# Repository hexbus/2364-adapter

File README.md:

# 2364 / 68764 ROM adapter

A compact **23 × 37 mm** adapter for replacing a 24-pin, active-low-select
2364 or MCM68764 ROM with a **28-pin AT28C64B EEPROM or 5 V 2764/27C64 EPROM**.
Designed by **Jon Guidry / hexbus** for the TI-99/4A Hexbus interface.

All 13 address lines and 8 data lines pass through without rearranging the
ROM image. Host pin 20 drives both `/CE` and `/OE`; replacement pin 27 is
held high to disable writing/programming. Program the memory separately.

## Top and bottom

| Top — components and ROM socket | Bottom — pins toward the host |
| --- | --- |
|  |  |

Previews show the delivered Gerbers; the bottom is viewed from underneath.
**C1, JP1 and `U1 NOTCH` identify the top. `J1 TO HOST` identifies the bottom.**
Each connector has its own square pin-1 pad; their positions are offset.
Both notch ends face the same end of the board.
The notched top silkscreen outline encloses all 28 memory pads and is centered
on the two U1 pin rows; the notch is at the pin-1 end.

[Photo of the first bare boards](images/first-boards.jpg): top on the left,
bottom on the right. Those boards predate the printed designer credit and top outline.
For my own batches, I also use JLCPCB's order-time QR option for identifiers
such as `JDG001`–`JDG025`. Public Gerbers include permanent
`hexbus.com (c) 2026` credit so boards made by others are identified too.

## Files and fabrication

- **[Download the Gerber ZIP — Rev A with full top outline, 9 November 2026](https://github.com/hexbus/2364-adapter/raw/refs/heads/main/gerbers/2364-adapter-rev-a-full-outline-20261109.zip)**
- **[Order at JLCPCB using my referral link](https://jlcpcb.com/?from=RVDYTTLKZHK)**
- [KiCad 10 project](hardware/68764-to-28pin.kicad_pro),
  [schematic](hardware/68764-to-28pin.kicad_sch) and [BOM](hardware/bom.csv)

Download the Gerber ZIP, open JLCPCB through the referral link, and upload
the ZIP. Select **2 layers, 1.6 mm FR4 and 1 oz copper**; confirm the detected
board size is **23 × 37 mm** before ordering. The referral link does not
upload the files automatically. I may receive referral rewards for qualifying
new users.

Order **2 layers, 1.6 mm FR4, 1 oz copper, 23 × 37 mm**, with solder mask
on both sides and HASL or ENIG finish. Component holes are specified as
**0.80 mm plated through holes**. Minimum track width is 0.25 mm; design
clearance is 0.20 mm. No stencil or assembly files are included.

This package retains the October 21 mask correction, adds bottom designer
credit, includes a notched outline for the top memory, and moves C1/JP1 labels
clear of the mask openings. Copper, masks,
drill geometry and outline match corrected Rev A. **Do not fabricate the
original October 19 package:** its connector pads lacked mask openings.

## JP1 and C1

| Installed memory | JP1 | Effect |
| --- | --- | --- |
| AT28C64B, DIP28 | **OPEN** | Pin 1 isolated; pin 27 `/WE` held high |
| 5 V 2764 / 27C64, DIP28 | **CLOSED** with solder | Pin 1 VPP at +5 V for reading; pin 27 `/PGM` high |

**C1: 100 nF (0.1 µF), 0805 ceramic, X7R or X5R, at least 16 V.**
It bypasses +5 V to ground and is nonpolarized: either orientation is correct.
Change JP1 only with power removed. Other EEPROM models need their exact
datasheet checked; this does not cover every part called “2864.”

## Assembly

1. Solder C1 and set JP1 first; the memory body will cover them.
2. Fit **two 1×12 round-pin male strips underneath**, pins pointing toward
   the host; solder from above. Use socket-compatible mating pins around
   0.45–0.50 mm diameter, not thick square headers.
3. Fit **two 1×14 female socket strips on top**, 2.54 mm pitch and 15.24 mm
   between rows; solder underneath. A closed-base DIP socket can foul the
   other connector's solder tails, so use separate strips.
4. Keep top tails at least 0.5 mm below the memory body and underside tails
   at least 0.5 mm clear of exposed metal in the host. Check actual strip
   dimensions, pin engagement and enclosure clearance before seating.
5. With no memory installed, check the pin map below. J1 pins 24 and 12 must
   have no sustained short; C1 may cause a brief meter response.
6. Program and verify the memory separately, then insert it with U1 pin 1
   at its square pad. With host power off, align J1 pin 1 with the original
   socket's pin 1. Check clearance and do not force it.

Never apply programming voltage through the 24-pin host connector.

## Pinout and continuity checks

Package pin numbers are **viewed from the top**. The bottom footprint is
already flipped correctly in CAD; do not reverse its numbering again.
Grouped entries correspond in the order shown.

| J1: 2364 / 68764 host | Signal | U1: 28-pin memory |
| --- | --- | --- |
| 1–8 | A7, A6, A5, A4, A3, A2, A1, A0 | 3–10 |
| 9–11 | D0, D1, D2 | 11–13 |
| 12 | Ground | 14; C1 ground pad |
| 13–17 | D3, D4, D5, D6, D7 | 15–19 |
| 18 | A11 | 23 |
| 19 | A10 | 21 |
| 20 | Active-low select | 20 (`/CE`) and 22 (`/OE`) |
| 21 | A12 | 2 |
| 22 | A9 | 24 |
| 23 | A8 | 25 |
| 24 | +5 V | 28 and 27; also 1 if JP1 closed |
| No host connection | U1 pin 1 | JP1 pad 2; isolated from VCC if open |
| No host connection | U1 pin 26 | Unconnected |

Verify U1 pins **20/22 connect to J1 pin 20, not ground**; pin **27 connects
to +5 V**; and pin **1 follows the JP1 setting**.

## Compatibility and checks

Use a 5 V host socket with the pinout above and active-low select on pin 20.
The C64's separate BASIC (901226) and KERNAL (901227) 2364 sockets are
electrical candidates, but fit and operation with this board are untested.
Other 23xx ROMs, 2332 character ROMs, different select polarities and later
combined 28-pin ROMs require separate checks. The adapter cannot supply a
missing host address bit or repair 4K-only decoding.

ERC/DRC, independent pin mapping, exported copper/masks/outline/drills and
the exact ZIP were checked; manufacturing layers were rendered and visually
inspected. All 52 connector pads have mask openings on both sides, with four
additional C1/JP1 openings on top. The mask check rejects the original defect.
Bare boards have been fabricated and photographed; assembled continuity,
soldering, fit, timing and host operation remain unverified.

Pin references: [Motorola MCM68764](https://deramp.com/downloads/mfe_archive/050-Component%20Specifications/Motorola/Memory%20Components/Motorola%20MCM68764.pdf),
[Microchip AT28C64B](https://ww1.microchip.com/downloads/aemDocuments/documents/MPD/ProductDocuments/DataSheets/AT28C64B-64-Kbit-8Kx8-Parallel-EEPROM-with-Page-Write-and-Software-Data-Protection-DS20006432.pdf),
[ST M27C64A](https://media.digikey.com/pdf/Data%20Sheets/ST%20Microelectronics%20PDFS/m27c64a_Rev2006.pdf),
[MOS 2364 (printed page 2-112)](https://www.bitsavers.org/pdf/commodore/Commodore_Component_Data_Catalog_1981.pdf).

## License

Copyright © 2026 **Jon Guidry / hexbus**.

[MIT terms with an Additional Attribution Requirement](LICENSE), as used for
my Floppy-FFC-Adapter. Physical reproductions and derivatives must retain
the designer credit on the board itself. Do not remove, obscure or
misrepresent that credit. See the full license for its terms.

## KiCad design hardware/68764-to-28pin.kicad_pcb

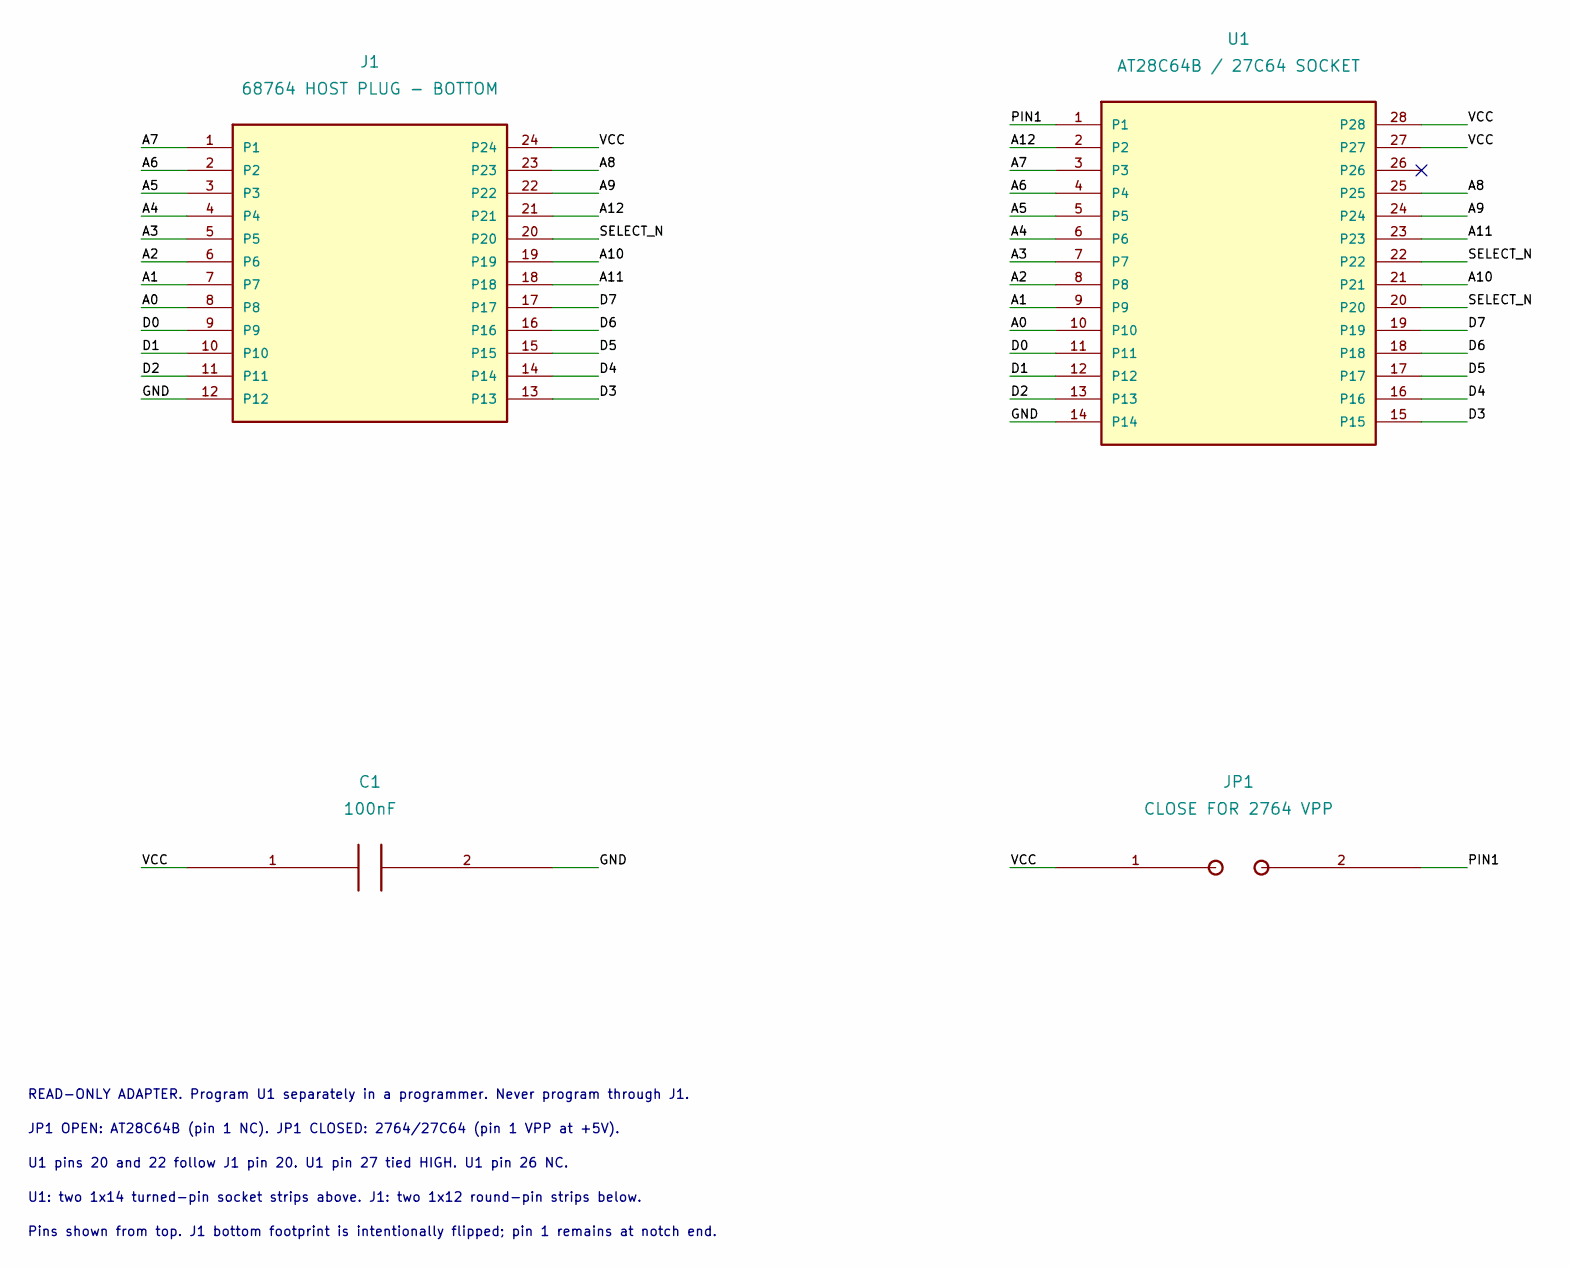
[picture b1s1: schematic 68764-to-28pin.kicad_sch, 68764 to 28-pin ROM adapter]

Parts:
C1: 100nF; C_0805
J1: 68764 HOST PLUG - BOTTOM; DIP24_Male_15.24mm
JP1: CLOSE FOR 2764 VPP; SolderJumper_Open
U1: AT28C64B / 27C64 SOCKET; DIP28_SocketStrips_15.24mm

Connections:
/A0: J1.8, U1.10
/A1: J1.7, U1.9
/A2: J1.6, U1.8
/A3: J1.5, U1.7
/A4: J1.4, U1.6
/A5: J1.3, U1.5
/A6: J1.2, U1.4
/A7: J1.1, U1.3
/A8: J1.23, U1.25
/A9: J1.22, U1.24
/A10: J1.19, U1.21
/A11: J1.18, U1.23
/A12: J1.21, U1.2
/D0: J1.9, U1.11
/D1: J1.10, U1.12
/D2: J1.11, U1.13
/D3: J1.13, U1.15
/D4: J1.14, U1.16
/D5: J1.15, U1.17
/D6: J1.16, U1.18
/D7: J1.17, U1.19
/GND: C1.2, J1.12, U1.14
/PIN1: JP1.2, U1.1
/SELECT_N: J1.20, U1.20, U1.22
/VCC: C1.1, J1.24, JP1.1, U1.27, U1.28

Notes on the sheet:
READ-ONLY ADAPTER. Program U1 separately in a programmer. Never program through J1.
JP1 OPEN: AT28C64B (pin 1 NC). JP1 CLOSED: 2764/27C64 (pin 1 VPP at +5V).
U1 pins 20 and 22 follow J1 pin 20. U1 pin 27 tied HIGH. U1 pin 26 NC.
U1: two 1x14 turned-pin socket strips above. J1: two 1x12 round-pin strips below.
Pins shown from top. J1 bottom footprint is intentionally flipped; pin 1 remains at notch end.

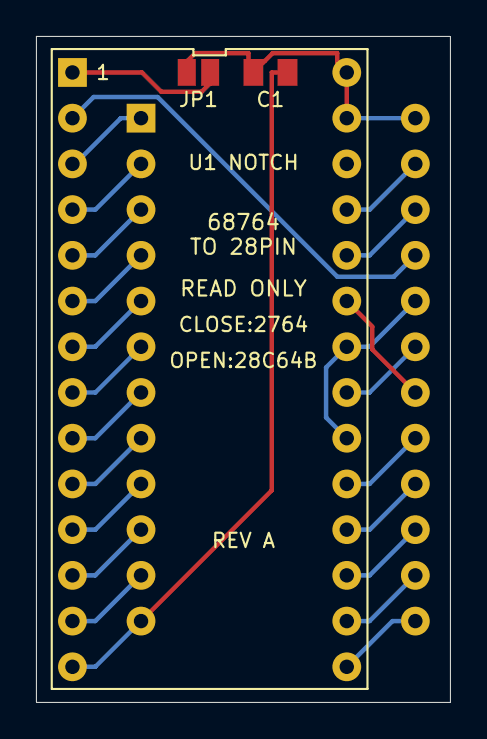
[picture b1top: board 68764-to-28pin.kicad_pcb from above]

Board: 2 copper layers, 23.0 x 37.0 mm, 4 parts (1 on the bottom side), 25 nets.
